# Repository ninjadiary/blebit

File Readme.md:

# BLE:Bit Tool

## Who

The BLE:Bit tool is developed and maintained by [Theodoros Danos.](https://twitter.com/fand0mas) 

## What

BLE:Bit is an open source tool to assist in Bluetooth Low Energy security auditing. Also, it is a tool that can be used in a development project, while it permits a connection to any BLE device and helps to exchange data in GATT layer.

## Why

There are multiple BLE-related projects that enables to do pretty much everything, made by remarkable people. Even though such tools exist, BLE:Bit took a very different approach which allows room for more options and tweaks regarding the user configurations. BLE:Bit makes the job easy. It is easy create a program to connect to any device, and provides many connection-based configurations, PIN-based configurations and enough callbacks with the appropriate BLE-standard error codes. With the appropriate errors one can troubleshoot and debug BLE-based devices in a more straightforward way. Some tools are provided, but the BLE:Bit tool is mostly built as a tool for finding vulnerabilities by creating tools-per-need, rather than to be used as "execute allthethings". Also, it makes the entrance to BLE-world very easy even for BLE-rookies.

## How

BLE:Bit is divided in two units: Central and Peripheral

Central, works as a "client", as it helps to connect to other BLE:Bit devices.

Peripheral, works as a "server" when other devices connect to the device, offering various services defined by the user

Multiple tools have been developed by the author, but you are free to use the BLE:Bit SDK provided in this repository to make your own tools. The tools developed are only Proof-of-Concept programs of what actually the SDK can do. The full potential of the tool lies on the SDK and not on the tools.

The BLE:Bit tool is consisted by both software and hardware. Regarding the hardware, schematics and firmware, can be found in "hw" directory, while the software is hosted in "src" directory.

If you wish to receive a BLE:Bit hardware with the latest firmware, it can be purchased at [shellwanted.com](https://shop.shellwanted.com/), even though i dare you to create one by yourself.

**For SDK documentation & examples visit**: [docs.blebit.io](https://docs.blebit.io)

**Case Study Projects** @ [shellwanted.com](https://shellwanted.com)

## MIT License

Copyright (c) 2022 Theodoros Danos

Permission is hereby granted, free of charge, to any person obtaining a copy
of this software and associated documentation files (the "Software"), to deal
in the Software without restriction, including without limitation the rights
to use, copy, modify, merge, publish, distribute, sublicense, and/or sell
copies of the Software, and to permit persons to whom the Software is
furnished to do so, subject to the following conditions:

The above copyright notice and this permission notice shall be included in all
copies or substantial portions of the Software.

THE SOFTWARE IS PROVIDED "AS IS", WITHOUT WARRANTY OF ANY KIND, EXPRESS OR
IMPLIED, INCLUDING BUT NOT LIMITED TO THE WARRANTIES OF MERCHANTABILITY,
FITNESS FOR A PARTICULAR PURPOSE AND NONINFRINGEMENT. IN NO EVENT SHALL THE
AUTHORS OR COPYRIGHT HOLDERS BE LIABLE FOR ANY CLAIM, DAMAGES OR OTHER
LIABILITY, WHETHER IN AN ACTION OF CONTRACT, TORT OR OTHERWISE, ARISING FROM,
OUT OF OR IN CONNECTION WITH THE SOFTWARE OR THE USE OR OTHER DEALINGS IN THE
SOFTWARE.

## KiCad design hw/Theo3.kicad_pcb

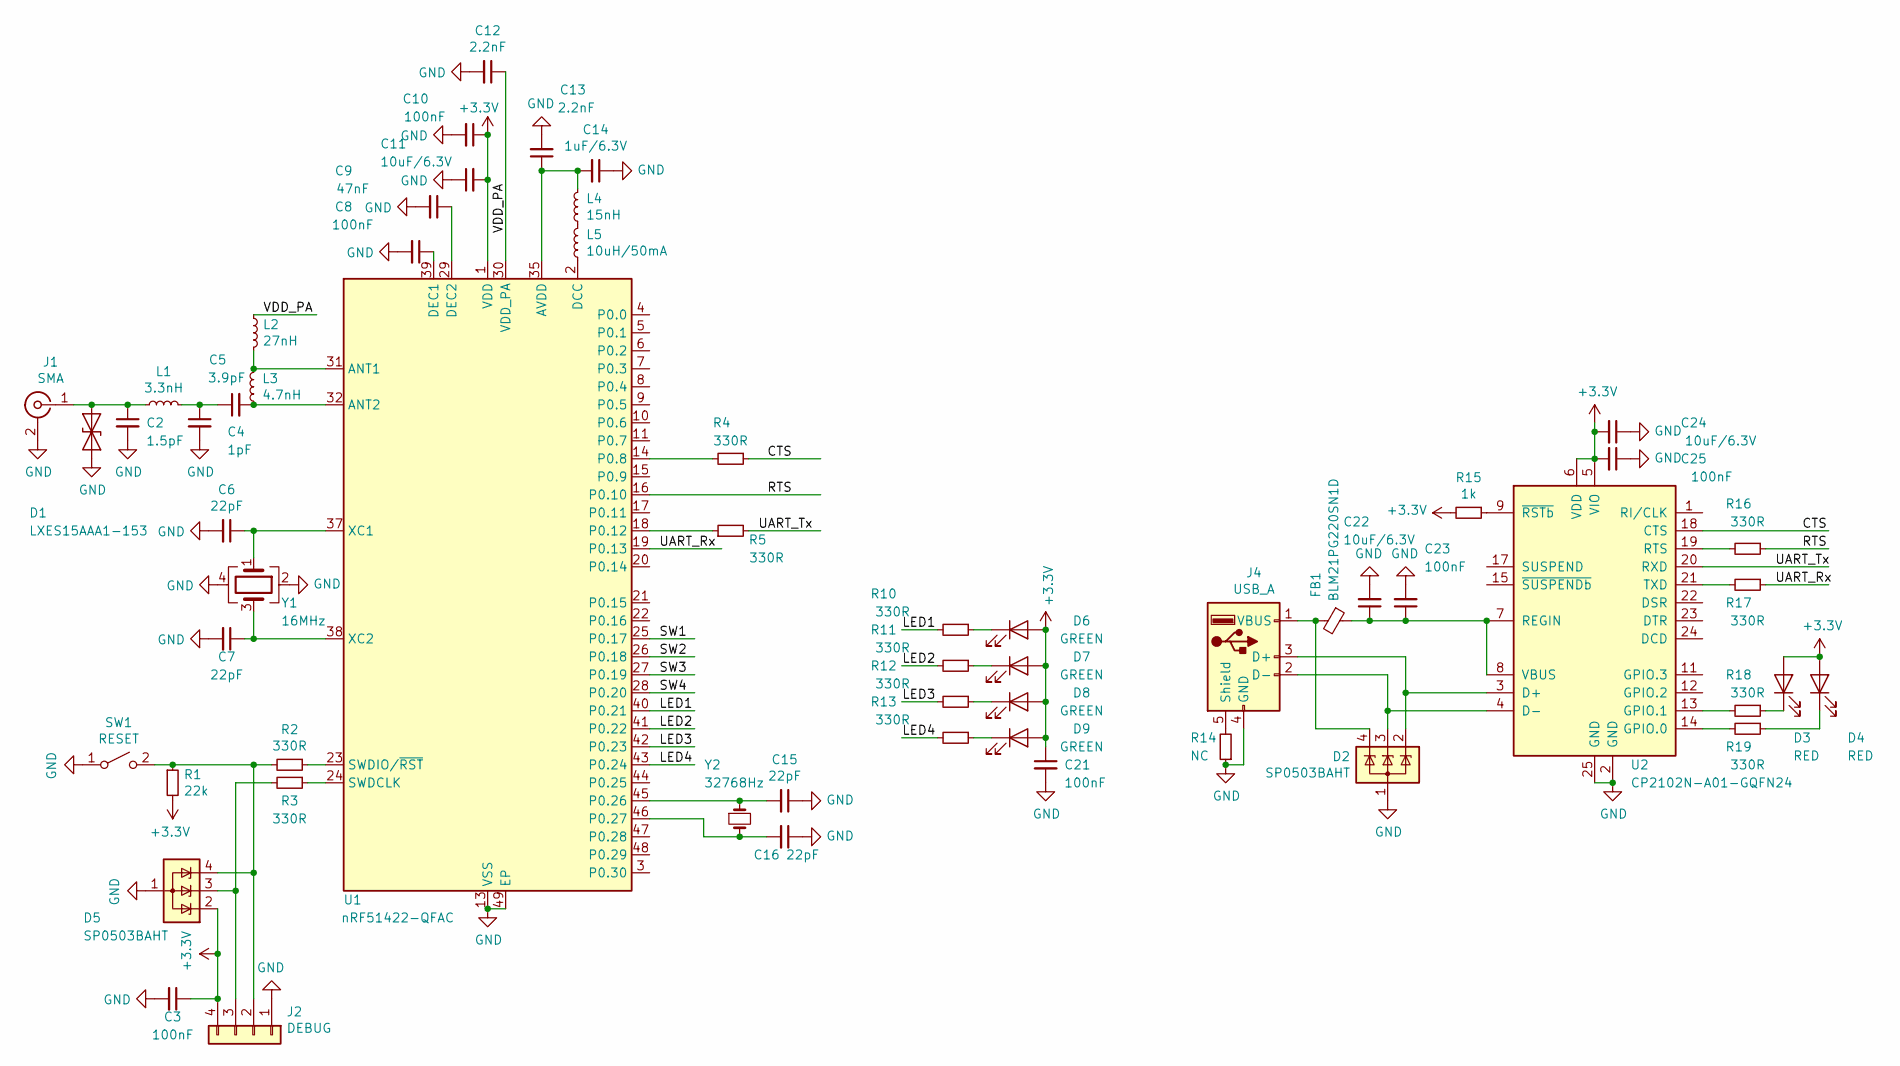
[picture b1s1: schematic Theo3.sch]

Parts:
C2: 1.5pF; C_0402_1005Metric
C3, C8, C10, C21, C23, C25: 100nF; C_0402_1005Metric
C4: 1pF; C_0402_1005Metric
C5: 3.9pF; C_0402_1005Metric
C6, C7, C15, C16: 22pF; C_0402_1005Metric
C9: 47nF; C_0402_1005Metric
C11, C22, C24: 10uF/6.3V; C_0603_1608Metric
C12, C13: 2.2nF; C_0402_1005Metric
C14: 1uF/6.3V; C_0402_1005Metric
D1: LXES15AAA1-153; C_0402_1005Metric
D2, D5: SP0503BAHT; SOT-143R_Reverse
D3, D4: RED; LED_0603_1608Metric
D6, D7, D8, D9: GREEN; LED_0603_1608Metric
FB1: BLM21PG220SN1D; C_0805_2012Metric
J1: SMA; SMA_Samtec_SMA-J-P-X-ST-EM1_EdgeMount
J2: DEBUG; PinHeader_1x04_P2.54mm_Vertical
J4: USB_A; USB_A_CNCTech_1001-011-01101_Horizontal
L1: 3.3nH; C_0603_1608Metric
L2: 27nH; C_0603_1608Metric
L3: 4.7nH; C_0603_1608Metric
L4: 15nH; L_0603_1608Metric
L5: 10uH/50mA; L_0603_1608Metric
R1: 22k; R_0402_1005Metric
R2, R3, R4, R5, R10, R11, R12, R13, R16, R17, R18, R19: 330R; R_0402_1005Metric
R14: NC; R_0603_1608Metric
R15: 1k; R_0402_1005Metric
SW1: RESET; SW_SPST_B3S-1000
U1: nRF51422-QFAC; QFN-48-1EP_6x6mm_P0.4mm_EP4.6x4.6mm
U2: CP2102N-A01-GQFN24; QFN-24-1EP_4x4mm_P0.5mm_EP2.6x2.6mm
Y1: 16MHz; Crystal_SMD_EuroQuartz_X22-4Pin_2.5x2.0mm
Y2: 32768Hz; Crystal_SMD_EuroQuartz_EQ161-2Pin_3.2x1.5mm

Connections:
+3V3: C3.1, C10.1, C11.2, C21.1, C24.2, C25.2, D3.2 (A), D4.2 (A), D5.2 (K), D6.2 (A), D7.2 (A), D8.2 (A), D9.2 (A), J2.4, R1.2, R15.2, U1.1 (VDD), U1.12 (VDD), U2.5 (VIO), U2.6 (VDD)
/CTS: R4.1, U2.18 (CTS)
/LED1: R10.2, U1.40 (P0.21)
/LED2: R11.2, U1.41 (P0.22)
/LED3: R12.2, U1.42 (P0.23)
/LED4: R13.2, U1.43 (P0.24)
/RTS: R16.1, U1.16 (P0.10)
/SW1: U1.25 (P0.17)
/SW2: U1.26 (P0.18)
/SW3: U1.27 (P0.19)
/SW4: U1.28 (P0.20)
/UART_Rx: R17.1, U1.19 (P0.13)
/UART_Tx: R5.2, U2.20 (RXD)
/VDD_PA: C12.1, L2.1, U1.30 (VDD_PA)
GND: C2.2, C3.2, C4.2, C6.2, C7.2, C8.2, C9.2, C10.2, C11.1, C12.2, C13.2, C14.1, C15.1, C16.1, C21.2, C22.2, C23.2, C24.1, C25.1, D1.2 (A2), D2.1 (A), D5.1 (A), J1.2 (Ext), J2.1, J4.4 (GND), R14.1, SW1.1 (A), U1.13 (VSS), U1.33 (VSS), U1.34 (VSS), U1.49 (EP), U2.2 (GND), U2.25 (GND), Y1.2, Y1.4
unnamed: C2.1, D1.1 (A1), J1.1 (In), L1.1
unnamed: C4.1, C5.1, L1.2
unnamed: C5.2, L3.1, U1.32 (ANT2)
unnamed: C6.1, U1.37 (XC1), Y1.1
unnamed: C7.1, U1.38 (XC2), Y1.3
unnamed: C8.1, U1.39 (DEC1)
unnamed: C9.1, U1.29 (DEC2)
unnamed: C13.1, C14.2, L4.2, U1.35 (AVDD), U1.36 (AVDD)
unnamed: C15.2, U1.45 (P0.26), Y2.1
unnamed: C16.2, U1.46 (P0.27), Y2.2
unnamed: C22.1, C23.1, FB1.1, U2.7 (REGIN), U2.8 (VBUS)
unnamed: D2.2 (K), J4.3 (D+), U2.3 (D+)
unnamed: D2.3 (K), J4.2 (D-), U2.4 (D-)
unnamed: D2.4 (K), FB1.2, J4.1 (VBUS)
unnamed: D3.1 (K), R18.1
unnamed: D4.1 (K), R19.1
unnamed: D5.3 (K), J2.3, R3.2
unnamed: D5.4 (K), J2.2, R1.1, R2.2, SW1.2 (B)
unnamed: D6.1 (K), R10.1
unnamed: D7.1 (K), R11.1
unnamed: D8.1 (K), R12.1
unnamed: D9.1 (K), R13.1
unnamed: J4.5 (Shield), R14.2
unnamed: L2.2, L3.2, U1.31 (ANT1)
unnamed: L4.1, L5.2
unnamed: L5.1, U1.2 (DCC)
unnamed: R2.1, U1.23 (SWDIO/~RST)
unnamed: R3.1, U1.24 (SWDCLK)
unnamed: R4.2, U1.14 (P0.8)
unnamed: R5.1, U1.18 (P0.12)
unnamed: R15.1, U2.9 (~RSTb)
unnamed: R16.2, U2.19 (RTS)
unnamed: R17.2, U2.21 (TXD)
unnamed: R18.2, U2.13 (GPIO.1)
unnamed: R19.2, U2.14 (GPIO.0)

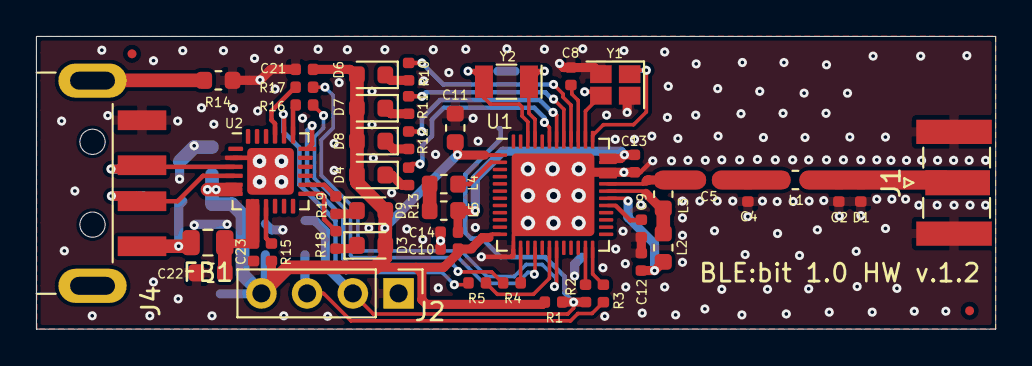
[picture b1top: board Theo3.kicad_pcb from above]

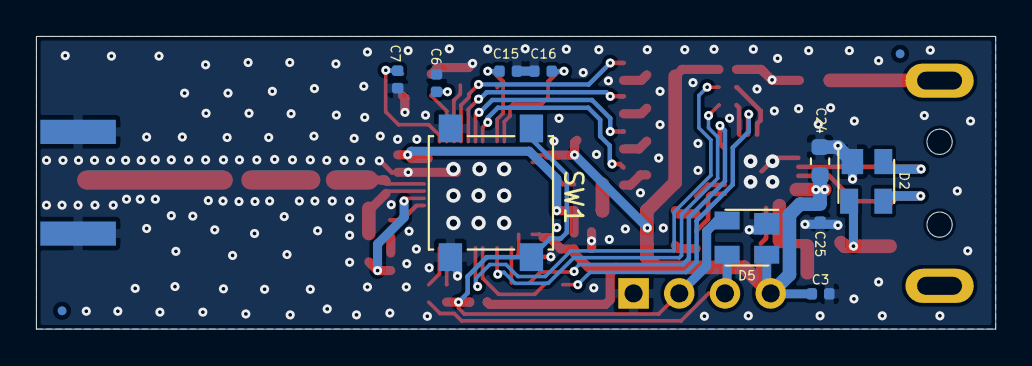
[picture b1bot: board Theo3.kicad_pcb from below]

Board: 2 copper layers, 53.3 x 16.3 mm, 58 parts (10 on the bottom side), 46 nets.

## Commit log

2021-05-26 Launch time
2021-05-27 Fixed bug with parser
2021-05-27 Add Example minipadlock
2021-05-27 example padlock added
2021-05-27 corrected error msg
2021-05-28 added license
2021-06-03 added new tools
2021-06-03 added android client
2021-06-05 added dependency jars
2021-06-08 added scanner
2021-06-09 added enumerator
2021-07-18 add license
2021-07-19 Update LICENSE
2022-02-22 firmware_added
2022-03-28 jar-removal
2022-03-28 update-dep
2022-05-04 reorganizing & fixing repairing bug
2022-05-09 notification bug fixed
2022-05-09 tool added
2022-05-09 renamed
2022-05-11 release
2022-05-11 updated v19
2022-07-07 fix concurrency bug
2022-10-06 sdk vers. updated
2022-10-06 fixed bugs
2022-10-09 reflects new mitm changes
